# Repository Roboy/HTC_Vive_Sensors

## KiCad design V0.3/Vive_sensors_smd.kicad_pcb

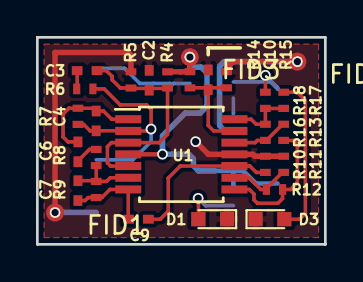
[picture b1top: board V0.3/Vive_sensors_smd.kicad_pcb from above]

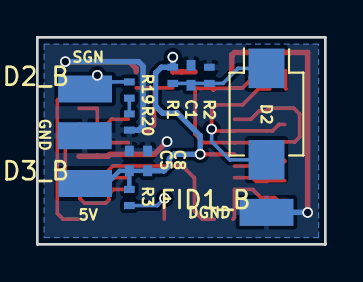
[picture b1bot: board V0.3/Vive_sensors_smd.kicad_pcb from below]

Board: 2 copper layers, 16.0 x 11.5 mm, 44 parts (16 on the bottom side), 20 nets.

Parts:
5V: 5V; SolderWirePad_single_SMD_1.5x3mm
C1, C2, C3, C5, C10: 100n; C_0402_NoSilk
C4, C7: 10p; C_0402_NoSilk
C6, C8, C9: 1u; C_0402_NoSilk
D1: Pwr_LED; LED_0603
D2: BPW34; PhotoDiode_SMD-DIL2_4.5x4
D3: Sgn_LED; LED_0603
DGND: D_GND; SolderWirePad_single_SMD_1.5x3mm
FID1, FID1_B, FID2, FID2_B, FID3, FID3_B: Fiducial_1mm_Dia_2.54mm_Outer_CopperTop
GND: GND; SolderWirePad_single_SMD_1.5x3mm
R1, R7, R10, R11: 10k; R_0402_NoSilk
R2: 22k; R_0402_NoSilk
R3, R6, R17, R18, R19, R20: 1k; R_0402_NoSilk
R4, R5, R9, R14, R15, R16: 100k; R_0402_NoSilk
R8: 2k; R_0402_NoSilk
R12: 47k; R_0402_NoSilk
R13: 4.7k; R_0402_NoSilk
SGN: Sgn; SolderWirePad_single_SMD_1.5x3mm
U1: TLV4316; TSSOP-14_4.4x5mm_Pitch0.65mm

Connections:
+5V: 5V.1, C5.2, C8.2, R1.1, R3.1, R4.1, R14.1, U1.4
GND: C1.2, C2.2, C5.1, C8.1, C10.2, D1.1, D3.1, DGND.1, GND.1, R2.2, R5.2, R10.2, R11.2, R15.2, R20.1, U1.11
unnamed: C1.1, D2.1, R1.2, R2.1
unnamed: C2.1, C3.1, R4.2, R5.1, U1.3, U1.5
unnamed: C3.2, R6.2
unnamed: C4.1, C6.2, R7.1, U1.1
unnamed: C4.2, D2.2, R6.1, R7.2, U1.2
unnamed: C6.1, R8.2
unnamed: C7.1, C9.2, R9.1, U1.7
unnamed: C7.2, R8.1, R9.2, U1.6
unnamed: C9.1, R10.1, U1.10
unnamed: C10.1, R14.2, R15.1, U1.13
unnamed: D1.2, R3.2
unnamed: D3.2, R17.1
unnamed: R18.1, R19.2, SGN.1
unnamed: R11.1, R12.2, U1.9
unnamed: R12.1, R13.2, U1.8
unnamed: R13.1, R16.2, U1.12
unnamed: R16.1, R17.2, R18.2, U1.14
unnamed: R19.1, R20.2

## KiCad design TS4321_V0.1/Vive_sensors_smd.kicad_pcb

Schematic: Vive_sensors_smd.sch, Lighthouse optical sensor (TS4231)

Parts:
C1: 1uF; C_0402
C2: 0.1uF; C_0402
D1: BPW34
J1: E; SolderWirePad_single_0-8mmDrill
J2: D; SolderWirePad_single_0-8mmDrill
J3: GND; SolderWirePad_single_0-8mmDrill
J4: 3.3V; SolderWirePad_single_0-8mmDrill
R1: 15k; R_0402
TS42311: TS4231

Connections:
+3V3: C1.1, C2.2, J4.1, TS42311.1 (A1), TS42311.9 (C3)
GND: C1.2, C2.1, J3.1, R1.1, TS42311.5 (B2), TS42311.6 (B3)
unnamed: D1.1 (K), TS42311.3 (A3)
unnamed: D1.2 (A), TS42311.2 (A2)
unnamed: J1.1, TS42311.8 (C2)
unnamed: J2.1, TS42311.7 (C1)
unnamed: R1.2, TS42311.4 (B1)

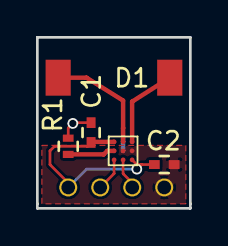
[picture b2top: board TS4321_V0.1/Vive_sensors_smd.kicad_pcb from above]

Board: 2 copper layers, 8.5 x 9.5 mm, 9 parts (0 on the bottom side), 7 nets.

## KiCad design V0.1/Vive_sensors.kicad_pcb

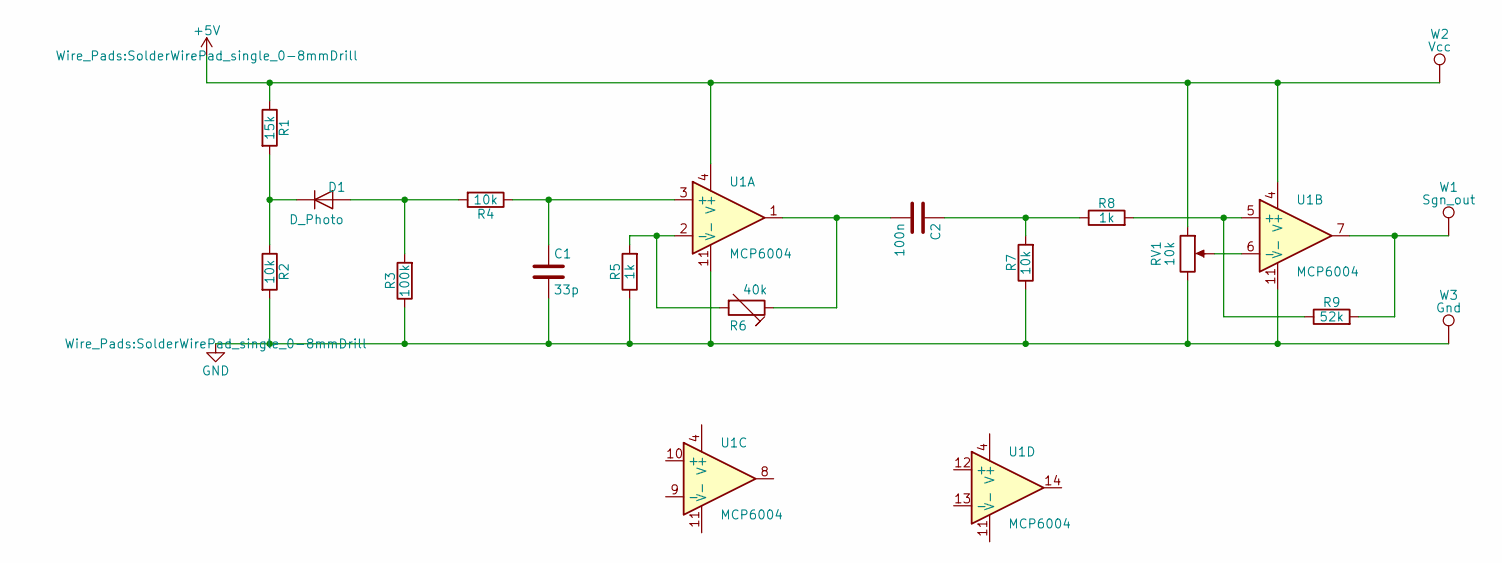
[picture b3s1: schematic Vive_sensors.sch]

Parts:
C1: 33p; C_Disc_D3.0mm_W1.6mm_P2.50mm
C2: 100n; C_Disc_D3.0mm_W1.6mm_P2.50mm
D1: D_Photo; D_T-1_P5.08mm_Horizontal
R1: 15k; R_Axial_DIN0204_L3.6mm_D1.6mm_P7.62mm_Horizontal
R2, R4, R7: 10k; R_Axial_DIN0204_L3.6mm_D1.6mm_P7.62mm_Horizontal
R3: 100k; R_Axial_DIN0204_L3.6mm_D1.6mm_P7.62mm_Horizontal
R5, R8: 1k; R_Axial_DIN0204_L3.6mm_D1.6mm_P7.62mm_Horizontal
R6: 40k; R_Axial_DIN0204_L3.6mm_D1.6mm_P7.62mm_Horizontal
R9: 52k; R_Axial_DIN0204_L3.6mm_D1.6mm_P7.62mm_Horizontal
RV1: 10k; Potentiometer_WirePads_Small
U1: MCP6004; TSSOP-14_4.4x5mm_Pitch0.65mm
W1: Sgn_out; SolderWirePad_single_0-8mmDrill
W2: Vcc; SolderWirePad_single_0-8mmDrill
W3: Gnd; SolderWirePad_single_0-8mmDrill

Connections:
+5V: R1.1, RV1.1, U1.4 (V+), W2.1
GND: C1.2, R2.2, R3.1, R5.1, R7.1, RV1.3, U1.11 (V-), W3.1
unnamed: C1.1, R4.1, U1.3 (+)
unnamed: C2.1, R7.2, R8.1
unnamed: C2.2, R6.1, U1.1
unnamed: D1.1 (K), R1.2, R2.1
unnamed: D1.2 (A), R3.2, R4.2
unnamed: R5.2, R6.2, U1.2 (-)
unnamed: R8.2, R9.1, U1.5 (+)
unnamed: R9.2, U1.7, W1.1
unnamed: RV1.2, U1.6 (-)

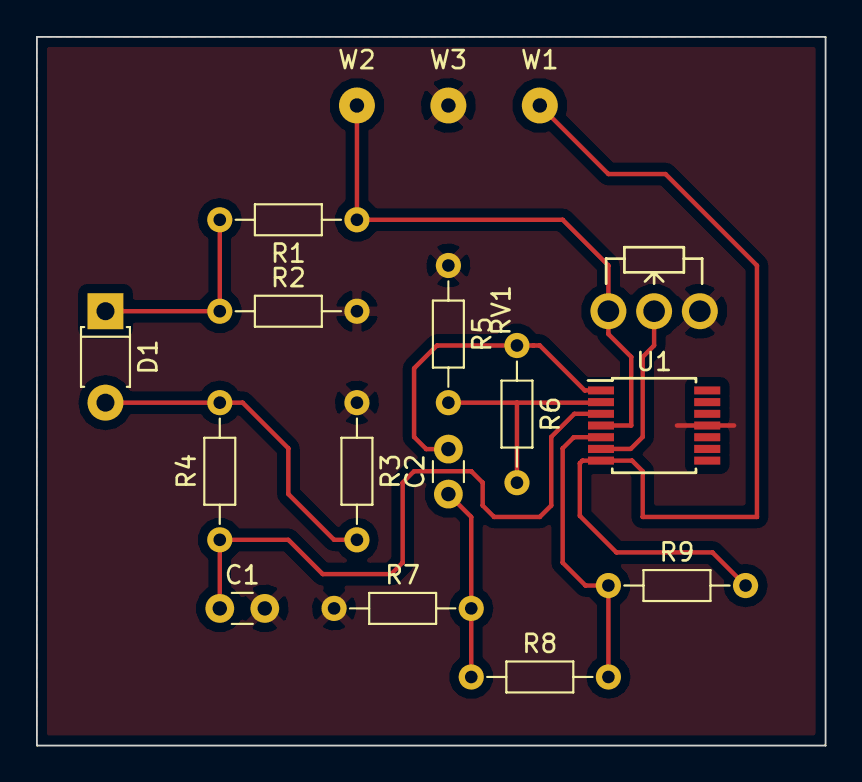
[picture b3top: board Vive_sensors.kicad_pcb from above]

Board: 2 copper layers, 43.8 x 39.4 mm, 17 parts (0 on the bottom side), 11 nets.

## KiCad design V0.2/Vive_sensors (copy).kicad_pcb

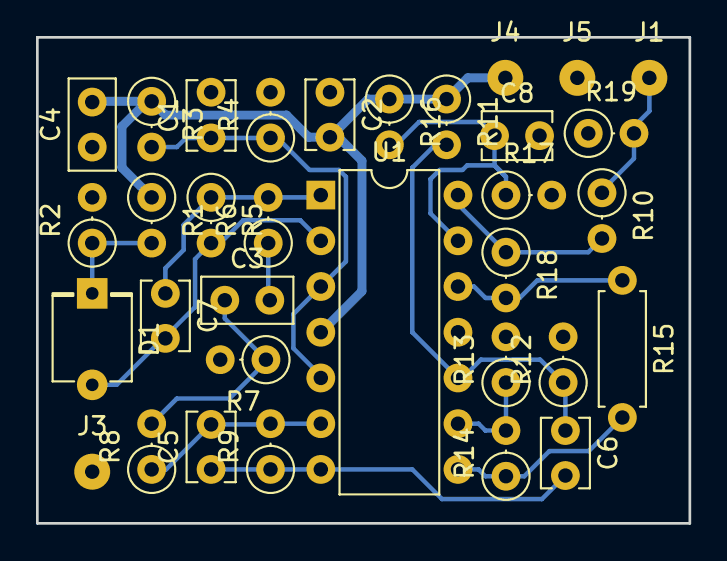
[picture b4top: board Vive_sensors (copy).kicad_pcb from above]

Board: 2 copper layers, 36.2 x 27.0 mm, 33 parts (0 on the bottom side), 17 nets.

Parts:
C1, C2, C8: 100n; C_Disc_D3.8mm_W2.6mm_P2.50mm
C3, C4: 1u; C_Disc_D5.0mm_W2.5mm_P2.50mm
C5, C7: 22p; C_Disc_D3.8mm_W2.6mm_P2.50mm
C6: 1u; C_Disc_D3.8mm_W2.6mm_P2.50mm
D1: BPW34; PhotoDiode_DIL2_4.3x4.65_RM5.08
J1: Sgn; SolderWirePad_single_0-8mmDrill
J3: D_GND; SolderWirePad_single_0-8mmDrill
J4: 12V; SolderWirePad_single_0-8mmDrill
J5: GND; SolderWirePad_single_0-8mmDrill
R1, R6, R13, R16, R17, R19: 10k; R_Axial_DIN0207_L6.3mm_D2.5mm_P2.54mm_Vertical
R2, R14: 22k; R_Axial_DIN0207_L6.3mm_D2.5mm_P2.54mm_Vertical
R3, R4, R5, R9, R18: 100k; R_Axial_DIN0207_L6.3mm_D2.5mm_P2.54mm_Vertical
R7: R; R_Axial_DIN0207_L6.3mm_D2.5mm_P2.54mm_Vertical
R8: 2.2k; R_Axial_DIN0207_L6.3mm_D2.5mm_P2.54mm_Vertical
R10: 27k; R_Axial_DIN0207_L6.3mm_D2.5mm_P2.54mm_Vertical
R11: 82k; R_Axial_DIN0207_L6.3mm_D2.5mm_P2.54mm_Vertical
R12: 12k; R_Axial_DIN0207_L6.3mm_D2.5mm_P2.54mm_Vertical
R15: 1k; R_Axial_DIN0207_L6.3mm_D2.5mm_P7.62mm_Horizontal
U1: TL074; DIP-14_W7.62mm

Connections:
+12V: C2.2, C4.2, J4.1, R1.1, R3.1, R11.1, R16.1, U1.4
GND: C1.2, C2.1, C4.1, C8.2, J3.1, J5.1, R2.2, R4.2, R7.2, R12.2, R13.2, R17.2, R19.1, U1.11
unnamed: C1.1, R3.2, R4.1, U1.3, U1.5
unnamed: C3.1, R7.1, R8.2
unnamed: C3.2, R6.1
unnamed: C5.1, C6.2, R9.1, U1.7
unnamed: C5.2, R8.1, R9.2, U1.6
unnamed: C6.1, R11.2, R12.1, U1.10
unnamed: C7.1, R5.1, R6.2, U1.1
unnamed: C7.2, D1.2, R5.2, U1.2
unnamed: C8.1, R16.2, R17.1, U1.13
unnamed: D1.1, R1.2, R2.1
unnamed: J1.1, R10.1, R19.2
unnamed: R10.2, R18.1, U1.14
unnamed: R13.1, R14.2, U1.9
unnamed: R14.1, R15.2, U1.8
unnamed: R15.1, R18.2, U1.12

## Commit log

2017-06-08 First commit for the already finished sensor boards. V0.1 and V0.2 are THT boards while V0.3 are the final SMT PCBs
2017-06-08 Added custom kicad library, for the solder pads
2017-08-03 optimized gain
2017-08-22 with laser cutted holding 7x7
2017-08-24 Arduino Testing Station
2017-09-04 with schematics for original htc vive sensor
2017-10-10 panelized v3.0
2017-11-12 with pick and place settings
2017-12-04 with TS4321
2017-12-04 with more drill holes in panel
2017-12-05 sensors revised by luis ;)
2018-01-17 with updated pick and place setup
2018-05-06 fixed 3.3V bug, with pcb outline
2018-05-08 with pick and place
2018-08-10 first flex
2018-08-10 with second version
2019-01-22 Updated resistor values for corrected gain
